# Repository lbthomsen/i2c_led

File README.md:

# i2c_led

Page on the STM32World wiki: [https://stm32world.com/wiki/I2C_RGB_LED_Board](https://stm32world.com/wiki/I2C_RGB_LED_Board_Development)

Youtube playlist with all the live streams: https://www.youtube.com/playlist?list=PLVfOnriB1RjW1bjvfdfvBH_yly3bV6s8T

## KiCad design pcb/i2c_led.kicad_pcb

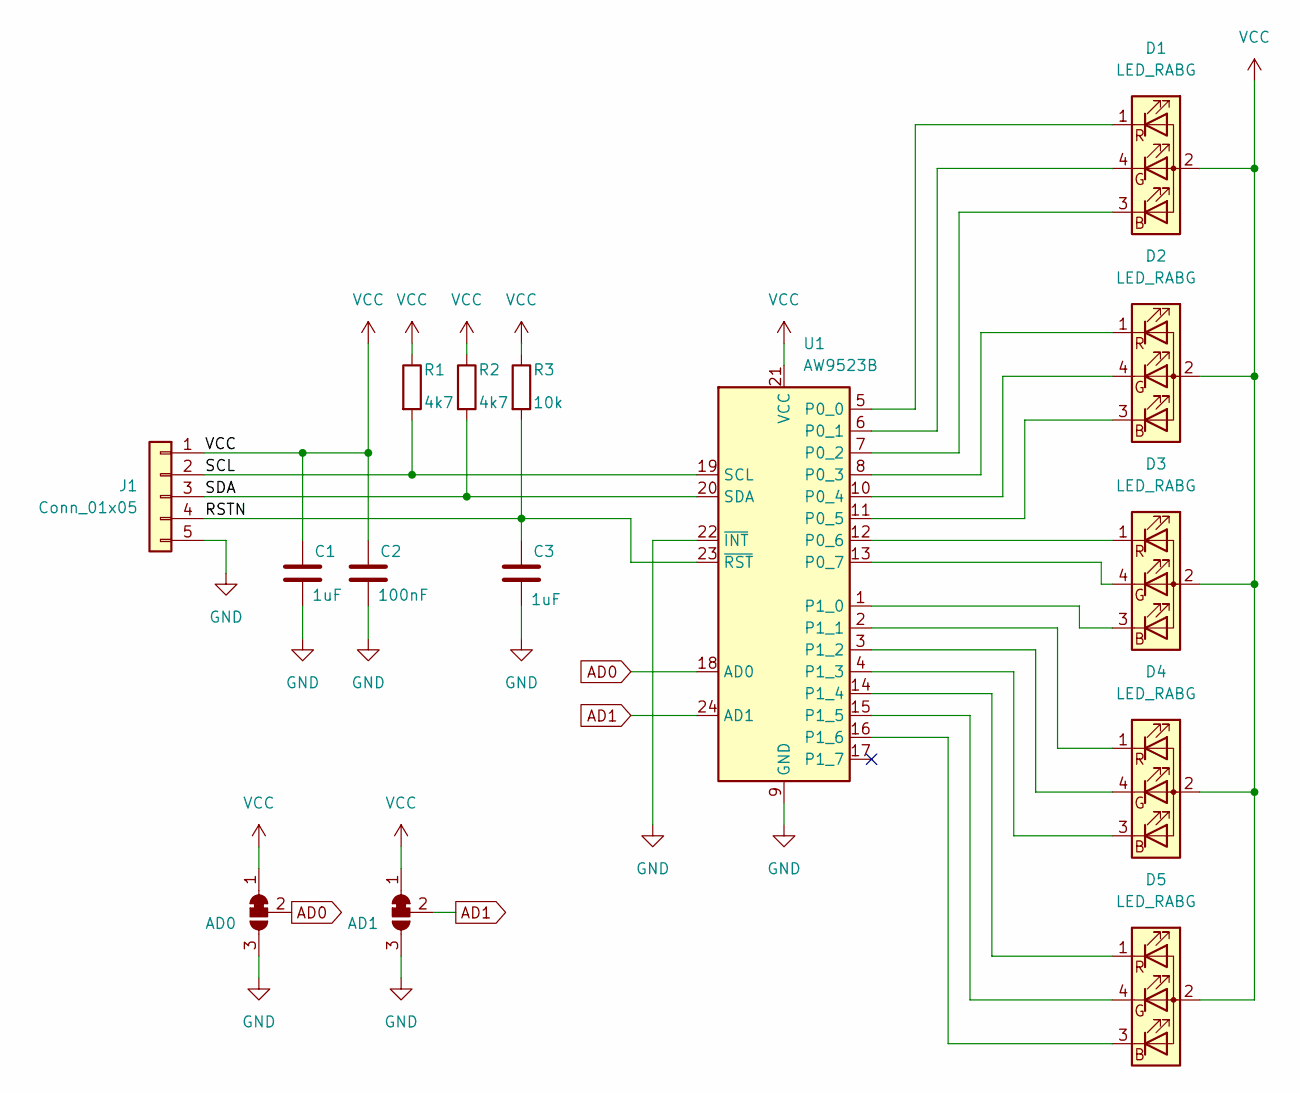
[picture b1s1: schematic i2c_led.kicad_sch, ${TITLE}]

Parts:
AD0, AD1: SolderJumper_3_Bridged12; SolderJumper-3_P1.3mm_Bridged2Bar12_RoundedPad1.0x1.5mm
C1, C3: 1uF; C_0603_1608Metric; LCSC C15849
C2: 100nF; C_0603_1608Metric; LCSC C14663
D1, D2, D3, D4, D5: LED_RABG; RGB; LCSC C965840
J1: Conn_01x05; PinHeader_1x05_P2.54mm_Vertical
R1, R2: 4k7; R_0603_1608Metric; LCSC C23162
R3: 10k; R_0603_1608Metric; LCSC C25804
U1: AW9523B; QFN-24-1EP_4x4mm_P0.5mm_EP2.7x2.7mm; LCSC C148077

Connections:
/RSTN: C3.1, J1.4, R3.2, U1.23 (~RST)
/SCL: J1.2, R1.2, U1.19 (SCL)
/SDA: J1.3, R2.2, U1.20 (SDA)
AD0: AD0.2 (C), U1.18 (AD0)
AD1: AD1.2 (C), U1.24 (AD1)
GND: AD0.3 (B), AD1.3 (B), C1.2, C2.2, C3.2, J1.5, U1.9 (GND), U1.22 (~INT), U1.25 (GND)
unnamed: D1.3 (BK), U1.7 (P0_2)
unnamed: D1.4 (GK), U1.6 (P0_1)
unnamed: D1.1 (RK), U1.5 (P0_0)
unnamed: D2.3 (BK), U1.11 (P0_5)
unnamed: D2.4 (GK), U1.10 (P0_4)
unnamed: D2.1 (RK), U1.8 (P0_3)
unnamed: D3.3 (BK), U1.1 (P1_0)
unnamed: D3.4 (GK), U1.13 (P0_7)
unnamed: D3.1 (RK), U1.12 (P0_6)
unnamed: D4.3 (BK), U1.4 (P1_3)
unnamed: D4.4 (GK), U1.3 (P1_2)
unnamed: D4.1 (RK), U1.2 (P1_1)
unnamed: D5.3 (BK), U1.16 (P1_6)
unnamed: D5.4 (GK), U1.15 (P1_5)
unnamed: D5.1 (RK), U1.14 (P1_4)
VCC: AD0.1 (A), AD1.1 (A), C1.1, C2.1, D1.2 (A), D2.2 (A), D3.2 (A), D4.2 (A), D5.2 (A), J1.1, R1.1, R2.1, R3.1, U1.21 (VCC)

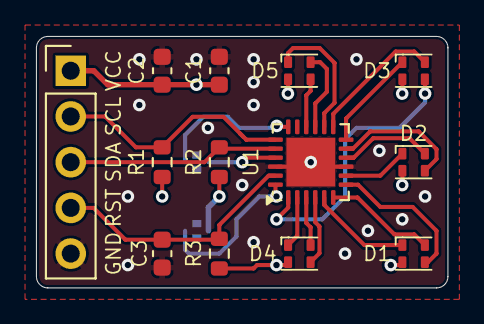
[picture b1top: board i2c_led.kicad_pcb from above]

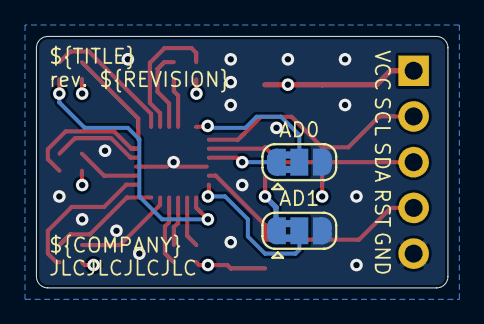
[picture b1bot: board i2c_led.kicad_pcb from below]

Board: 4 copper layers, 22.9 x 14.0 mm, 15 parts (2 on the bottom side), 22 nets.

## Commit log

2025-05-26 Project ongoing
2025-05-27 Done with second video https://youtube.com/live/dbczXZmWQ1s?feature=share
2025-05-27 Hmmm
2025-05-27 Tweaked after review
2025-05-27 Tweaks
2025-05-27 More tweaking
2025-05-28 Working version
2025-05-28 More tweaks - should be ready to order
2025-05-30 Moving workstation
2025-05-30 Ready to order
2025-06-12 Ready to order - rev_b
2025-06-16 Hmmmm
2025-06-23 Added firmware - working
2025-06-25 Created stm32f402 example
2025-06-26 Change
